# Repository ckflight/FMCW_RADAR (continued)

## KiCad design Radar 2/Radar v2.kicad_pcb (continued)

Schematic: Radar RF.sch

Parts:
C32, C35, C36, C41, C43, C44, C46, C49, C50, C51, C56, C58, C59, C66, C70, C80, C84, C85, C86, C87, C88, C109, C110: 100nF; SMD_0402
C33: 470pF; SMD_0402
C37, C38, C42: 18pF; SMD_0402
C39, C40, C52, C60, C61, C67, C68, C76: 10pF; SMD_0402
C45, C47, C48, C53, C79: 100pF; SMD_0402
C55: 330nF; SMD_0402
C57, C73, C74, C75, C77, C78: 10nF; SMD_0402
C62: 2.2nF; SMD_0402
C63, C64, C89: 10uF; SMD_0603
C65, C71: DNP; SMD_0402
C69: 2.2uF; SMD_0402
C72, C81, C82, C90: 1nF; SMD_0402
C83: 0.5pF; SMD_0402
D9, D10: Led_Diode; Diode_0603
L1, L4, L5, L8, L9: BLM18PG181SN1D; SMD_0603
L2, L3: 2.2uH; SMD_0603
L6: LQW18ANR10J00D; SMD_0603
L7: 0.6nH; SMD_0402
R2, R3, R33, R35: 0; SMD_0402
R25, R29, R59: 50; SMD_0402
R26: 5.49K; SMD_0402
R27, R28, R31, R75: DNP; SMD_0402
R30, R39, R40, R46, R49, R56, R79, R80: 1K; SMD_0402
R32: 240; SMD_0402
R36, R37: 4.7K; SMD_0402
R38: 100K; SMD_0402
R41, R42: 10K; SMD_0402
R43: 1.8; SMD_0402
R44, R45: 910; SMD_0402
R47, R48: 130; SMD_0402
R50, R51: 4.99K; SMD_0402
R52, R77, R78: 16.7; SMD_0402
R57: 0 to 27; SMD_0402
R58: 30K; SMD_0402
R76: 100; SMD_0402
U5, U10, U11, U14, U16, U24, U26, U34, U36, U46: Check_Point; SolderPad_1_1.5mm_SMD_Circle
U6: SG-210STF; Crystal_2.5x2mm
U7, U13: 5400BL15B050E; Balun_5400BL15B050E
U8: ADF4158; LFCSP24_4x4mm_P0.5mm_1EXP_2.5x2.5mm
U9: ADL5801; LFCSP24_4x4mm_P0.5mm_1EXP_2.5x2.5mm
U12: TLV172; SC70_5
U15: LT6232; SSOP16_3.9x4.9mm_P0.635mm
U17: HMC431LP4; QFN24_4x4mm_P0.5mm_1EXP_2.7x2.7mm
U18: TRF37A75; WSON8_2x2mm_P0.5mm_1EXP_0.9x1.6mm
U19, U27: PAT1220-C-6DB; PAT1220_6dB
U20: SKY65404; SKY65404_31
U21: TQP5523; QFN20_4x4mm_P0.5mm_1EXP_2.5x2.5mm
U22, U30: SMA_Connector
U23, U28, U42, U43, U44: MITERED_BEND; Mitered_Bend_0.33mm_90
U29: Directional_Coupler; Directional_Coupler_15dB

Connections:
+2.5: R46.2, R47.2, R48.1, R49.2, U15.3 (+), U15.5 (+); also elsewhere on the board
+3.0: L4.2; also elsewhere on the board
+3.3: C32.1, C35.1, C36.1, C37.1, C38.1, C109.1, L9.1, U6.1 (ST), U6.4 (VCC), U8.6 (AVDD), U8.7 (AVDD), U8.8 (AVDD), U8.18 (SDVDD), U8.19 (DVDD); also elsewhere on the board
+5: C41.2, C43.2, C44.2, C45.2, C47.2, C56.2, C58.1, C66.2, C71.1, C110.2, L1.2, L5.1, L8.1, R25.1, R29.2, R30.1, U9.7 (VPLO), U9.13 (VPDT), U9.18 (VPRF), U9.24 (VPLO), U15.4 (V+); also elsewhere on the board
+10: C59.1, U12.5 (V+); also elsewhere on the board
/Radar RF/LNA_3.3: C84.1, C86.1, D10.2 (A), L7.2, L9.2, R76.1
ADF_CE: U8.13 (CE); also elsewhere on the board
ADF_CLK: U8.14 (CLK); also elsewhere on the board
ADF_DATA: U8.15 (DATA); also elsewhere on the board
ADF_LE: U8.16 (LE); also elsewhere on the board
ADF_MUXOUT: U8.17 (MUX_OUT), U36.1; also elsewhere on the board
ADF_TXDATA: U8.12 (TXDATA); also elsewhere on the board
DAC_OUT1: R75.1, U11.1; also elsewhere on the board
DET_OUT: R58.1, U21.10 (DET), U24.1; also elsewhere on the board
GND: C32.2, C35.2, C36.2, C37.2, C38.2, C41.1, C42.2, C43.1, C44.1, C45.1, C46.2, C47.1, C48.2, C49.1, C50.1, C51.1, C53.1, C56.1, C57.2, C58.2, C59.2, C65.2, C66.1, C69.2, C70.2, C71.2, C75.2, C76.2, C79.2, C80.2, C83.2, C84.2, C85.2, C86.2, C87.1, C88.1, C89.1, C109.2, C110.1, R26.2, R31.2, R32.1, R37.2, R56.2, R58.2, R59.2, R79.2, R80.2, U6.2 (GND), U7.2 (GND), U7.5 (GND), U8.1 (CPGND), U8.2 (AGND), U8.3 (AGND), U8.10 (DGND), U8.11 (SDGND), U8.25 (EXP), U9.1 (GND), U9.2 (GND), U9.5 (GND), U9.6 (GND), U9.8 (GND), U9.12 (GND), U9.14 (GND), U9.17 (GND), U9.19 (GND), U9.23 (GND), U9.25 (EXP), U12.2 (V-), U13.2 (GND), U13.5 (GND), U15.13 (V-), U17.15 (GND), U17.25 (EXP), U18.3 (NC), U18.4 (NC), U18.5 (PWDN), U18.6 (NC), U18.8 (NC), U18.9 (GND), U19.3 (GND), U20.2 (GND), U20.5 (GND), U20.7 (EXP), U21.1 (GND), U21.2 (GND), U21.4 (GND), U21.11 (GND), U21.12 (GND), U21.14 (GND), U21.15 (GND), U21.16 (GND), U21.17 (GND), U21.21 (EXP), U22.2, U22.3, U22.4, U22.5, U27.3 (GND), U30.2, U30.3, U30.4, U30.5, U46.1; also elsewhere on the board
IF+: L2.1, R29.1, U5.1, U9.20 (IFOP)
IF-: L3.1, R25.2, U9.21 (IFON), U16.1
IFF+: R44.1, R50.1, U15.16; also elsewhere on the board
IFF-: R45.2, R51.1, U15.10; also elsewhere on the board
MIXER_EN: U9.9 (ENBL); also elsewhere on the board
MIXER_LO: U7.1 (IN), U23.2
unnamed: C33.1, U8.9 (REF_IN)
unnamed: C33.2, U6.3 (OUT)
unnamed: C39.1, U9.3 (LOIP)
unnamed: C39.2, U7.4 (OUTN)
unnamed: C40.1, U9.4 (LOIN)
unnamed: C40.2, U7.3 (OUTP)
unnamed: C42.1, C46.1, L1.1, U8.22 (VP)
unnamed: C48.1, U8.4 (RFINB)
unnamed: C49.2, C51.2, R27.2, R30.2, R31.1, U9.10 (VSET)
unnamed: C50.2, C53.2, R27.1, U9.11 (DETO)
unnamed: C52.1, U8.5 (RFINA)
unnamed: C52.2, U44.2
unnamed: C55.1, C57.1, R33.1, U8.24 (CP), U10.1
unnamed: C55.2, R28.2, R32.2
unnamed: C60.1, U13.4 (OUTN)
unnamed: C61.1, U13.3 (OUTP)
unnamed: C62.1, C63.2, L2.2
unnamed: C62.2, C64.2, L3.2
unnamed: C63.1, R39.1
unnamed: C64.1, R40.1
unnamed: C65.1, R38.1, U14.1, U17.22 (VTUNE)
unnamed: C67.1, R2.1, R41.2, U15.1, U26.1
unnamed: C67.2, R39.2, R41.1, U15.2 (-)
unnamed: C68.1, R3.1, R42.2, U15.7, U34.1
unnamed: C68.2, R40.2, R42.1, U15.6 (-)
unnamed: C69.1, C70.1, L4.1, U17.20 (VCC)
unnamed: C72.1, L6.1, U18.7 (RFOUT)
unnamed: C72.2, U42.2
unnamed: C73.1, C77.2, R44.2
unnamed: C73.2, R2.2
unnamed: C74.1, C78.2, R45.1
unnamed: C74.2, R3.2
unnamed: C75.1, C76.1, L6.2, R43.2
unnamed: C77.1, R47.1, U15.14 (+)
unnamed: C78.1, R48.2, U15.12 (+)
unnamed: C79.1, C80.1, L5.2, R43.1, U18.1 (VCC)
unnamed: C81.1, U20.4 (RF_OUT)
unnamed: C81.2, U18.2 (RFIN)
unnamed: C82.1, U21.3 (RFIN)
unnamed: C82.2, U19.2 (OUT)
unnamed: C83.1, U20.3 (RF_IN), U22.1
unnamed: C85.1, R57.2, U21.20 (VCC1)
unnamed: C87.2, C88.2, C89.2, L8.2, R57.1, U21.18 (VCC3), U21.19 (VCC2)
unnamed: C90.1, U29.1 (IN)
unnamed: C90.2, U21.13 (RFOUT)
unnamed: D9.1 (K), R79.1
unnamed: D10.1 (K), R80.1
unnamed: L7.1, U20.6 (VCC)
unnamed: R26.1, U8.23 (RSET)
unnamed: R28.1, U8.20 (SW1)
unnamed: R33.2, R75.2, U12.1 (+)
unnamed: R35.1, R38.2, U12.4
unnamed: R35.2, R36.1
unnamed: R36.2, R37.1, U12.3 (-)
unnamed: R46.1, R50.2, U15.15 (-)
unnamed: R49.1, R51.2, U15.11 (-)
unnamed: R52.1, U17.16 (RFOUT)
unnamed: R52.2, R77.1, R78.2
unnamed: R59.1, U29.4 (TRM)
unnamed: R76.2, U20.1 (V_ENA)
unnamed: R77.2, U19.1 (IN)
unnamed: R78.1, U43.2
unnamed: U13.1 (IN), U42.1
unnamed: U23.1, U28.1
unnamed: U27.1 (IN), U29.3 (CPL)
unnamed: U27.2 (OUT), U28.2
unnamed: U29.2 (OUT), U30.1
unnamed: U43.1, U44.1
PA_EN: D9.2 (A), R56.1, U21.5 (PA_EN); also elsewhere on the board
RFIN: C60.2, U9.15 (RFIN)
RFIP: C61.2, U9.16 (RFIP)

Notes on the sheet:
Scale 3.3V DAC output to 10V
Scale 5V PLL output to 10V
If DAC will be used change R35(0) with 4.7K to make gain 3
RC filter makes it noisy. I just placed 100K series resistor to filter noise.
Max 0dBm -4dBm input
-4dBm
29 to 37dB, typ. 32dB Gain OP1dB 31dBm Pout = 22 to 27dBm Pout = 21dBm 5V, 300mA
WYE -6dBm resistive splitter Zo/3 each apprx. 17 ohm
-10dBm
100mW rating
TX ANTENNA
16dB Directional Coupler
-16dB
Pout = 6 to 11 dBm - 6 dB = 0 to 5 dBm
Pout = 22 to 27dBm - 16dB = 6 to 11 dBm
RX ANTENNA
Max Input Power: 1dBm NF: 1dB Gain: 12dB at 6GHz IIP3: 9 dBm IP1dB: -4 dBm
Max 1dBm input to LNA
Max Input Power: 10 dBm NF: 4.0 dB Gain: 11 dB at 6 GHz OIP3: 23 dBm OP1dB: 12 dBm
-1dB Insertion Loss
Idd = 32mA max
Pout 2dBm @3v, 27mA
PI Type Attenuator Network 1 and 2 can be both in/out, directionless
@3.0 max 15mA
@5.0v, max 100mA
IIP3 28.5 dBm IP1dB 11dBm for 5-6GHz LO drive 0dBm @5v, max 200mA typ 130mA
Input 2 MHz LC low pass filter. 10uF for AC coupling capactior to remove DC offset. 1st stage opamp is amplifier. 2nd stage opamp is sallen key high pass filter IMPORTANT NOTE: Sallen Key filter calculator has oscillation calculation to show if it oscillates. Be careful when changing the numbers Th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
ADF4158 is Freq. Synthesizer to form a PLL topology. It requires a referance clock and an external VCO. It is not a PLL itself. It is used to drive VCO in a way the user wants. So it takes ref clock and VCO output and generates voltage through charge pump to generate the waveform wanted.(sawtooth e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
50 Ohm to 50 Ohm Balun for Single to Differential
4.5 to 5.25 range
30MHz
2.8 to 5.0 range
+2dBm Output
330nF 10nF 240 Ohm has no oscillation
Sallen Key filter requires isolation resistor to prevent oscillation. The capacitive load makes it unstable. To attenuate the peak value of 1.4MHz oscillation i changed differential to single ended 1K to 100 Ohm and added gain.

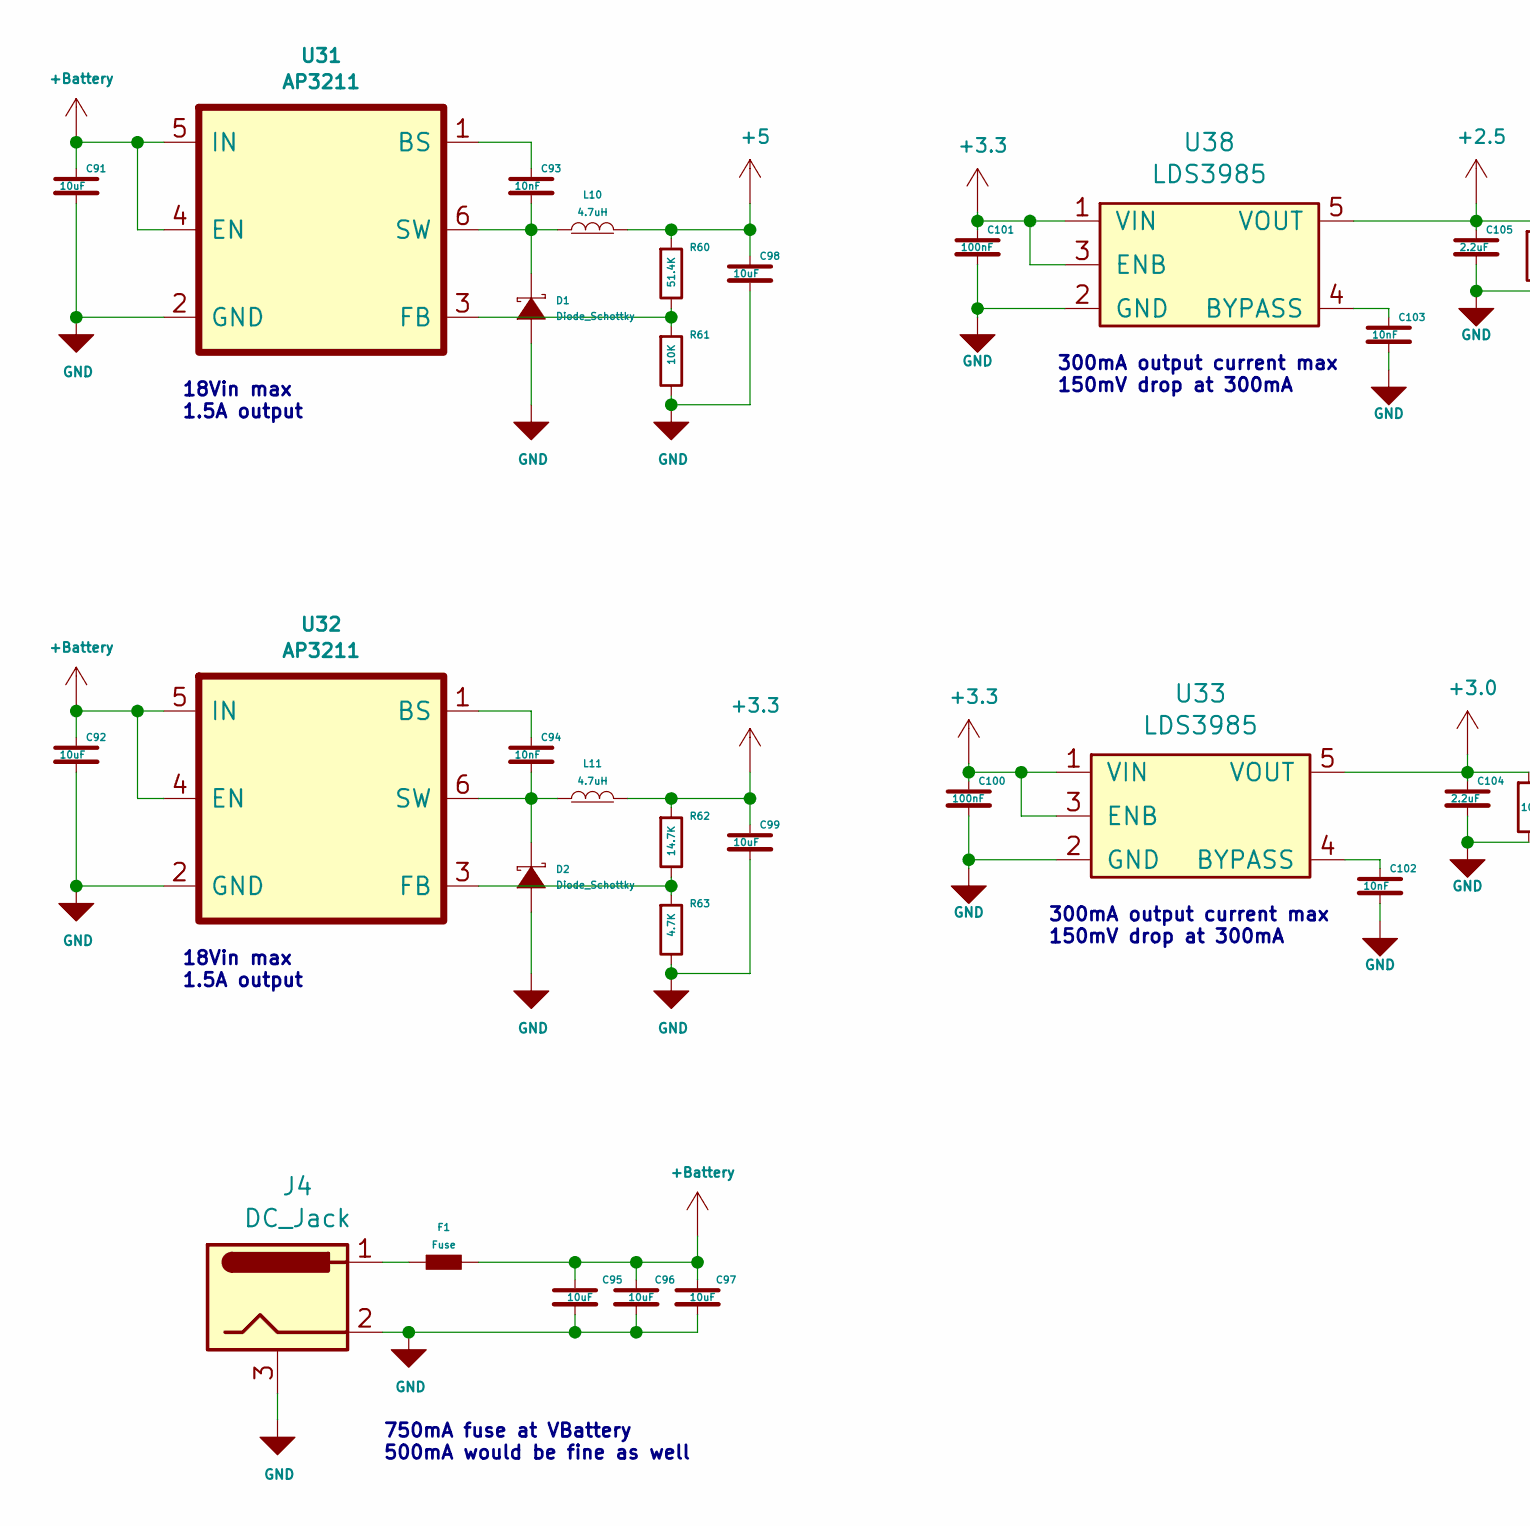
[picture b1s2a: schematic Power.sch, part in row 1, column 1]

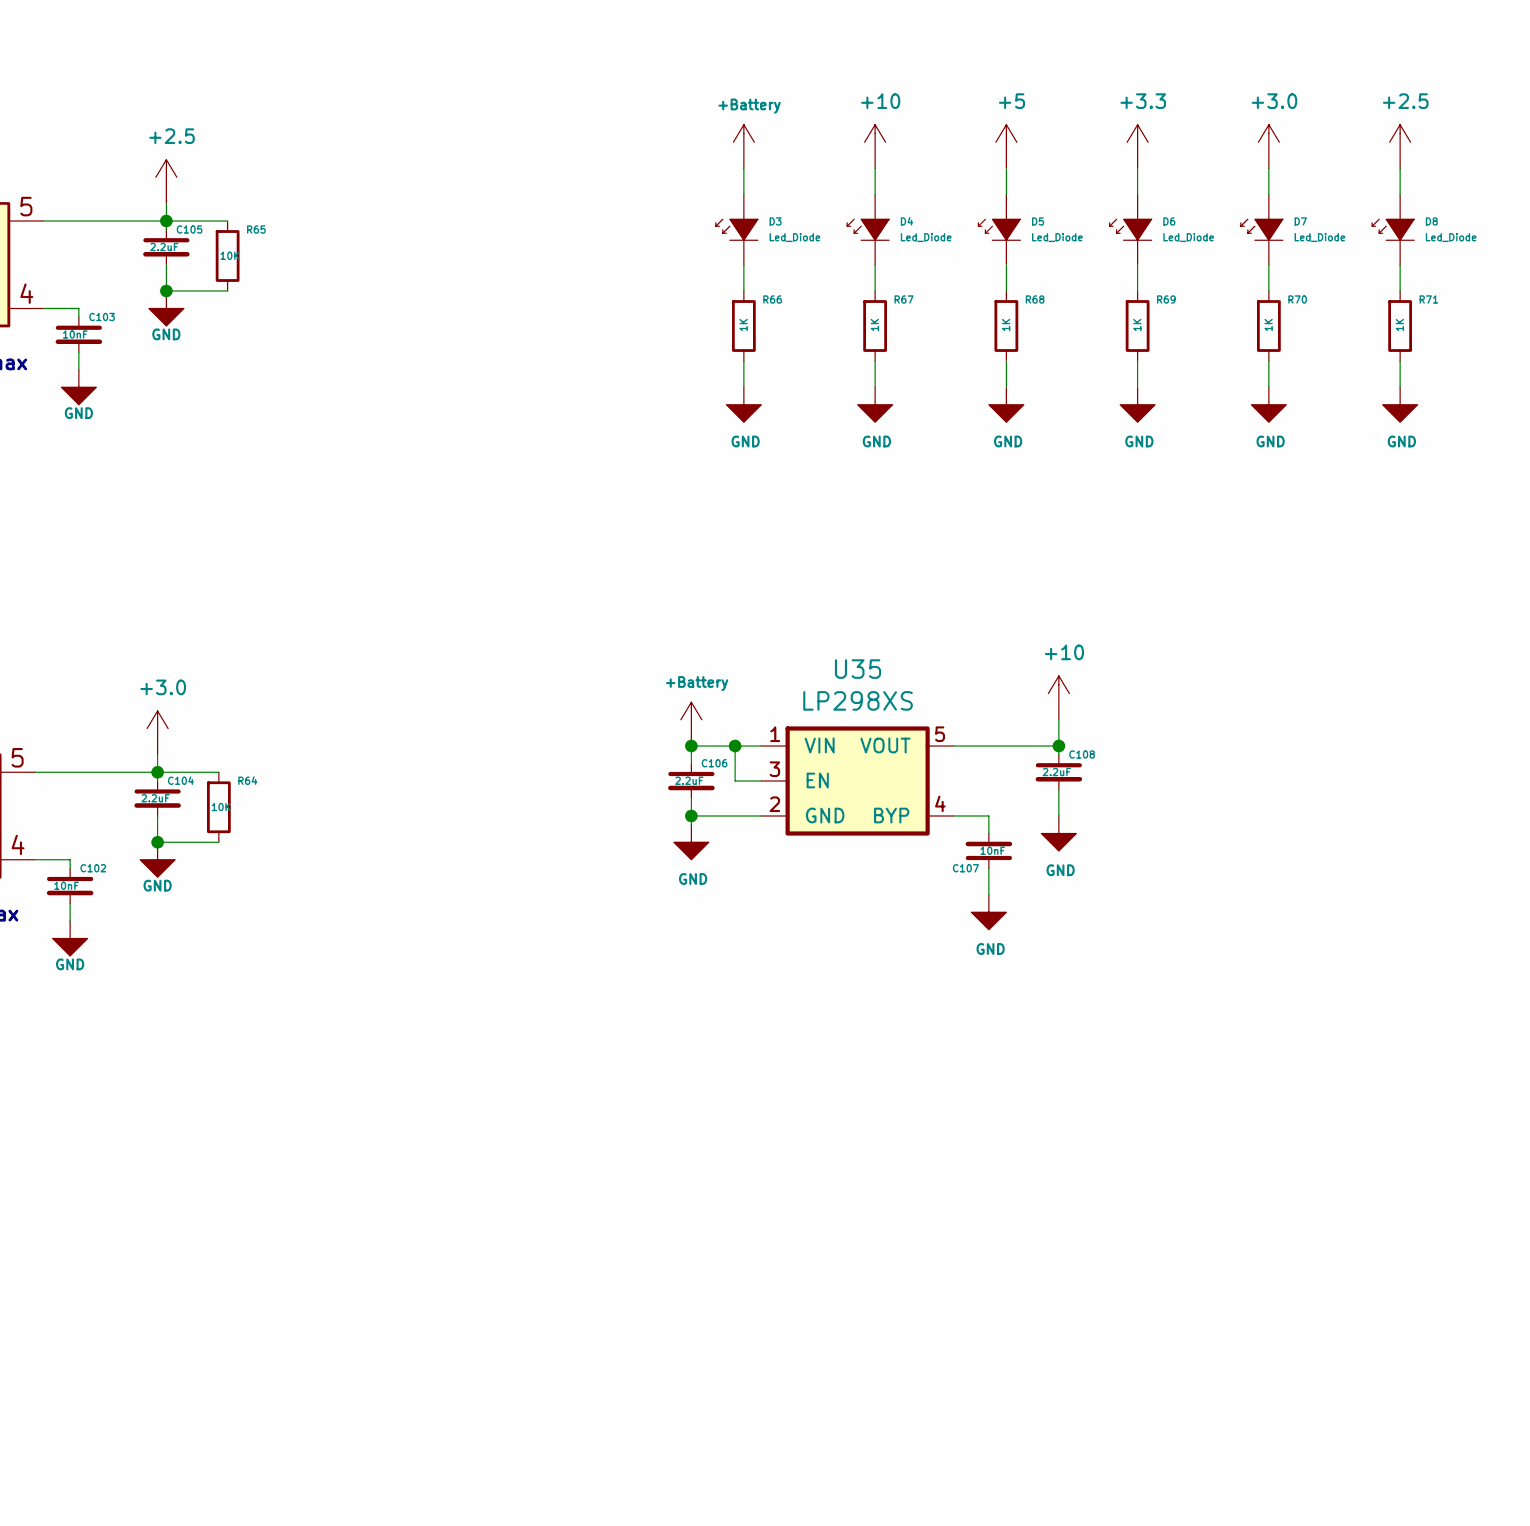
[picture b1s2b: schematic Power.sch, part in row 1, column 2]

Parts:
C91, C92, C95, C96, C97, C98, C99: 10uF; SMD_0603
C93, C94, C102, C103, C107: 10nF; SMD_0402
C100, C101: 100nF; SMD_0402
C104, C105, C106, C108: 2.2uF; SMD_0603
D1, D2: Diode_Schottky; Diode_SDM2U30CSP_7
D3, D4, D5, D6, D7, D8: Led_Diode; Diode_0603
F1: Fuse; SMD_0805
J4: DC_Jack; BarrelJack
L10, L11: 4.7uH; SMD_0805
R60: 51.4K; SMD_0402
R61, R64, R65: 10K; SMD_0402
R62: 14.7K; SMD_0402
R63: 4.7K; SMD_0402
R66, R67, R68, R69, R70, R71: 1K; SMD_0402
U31, U32: AP3211; SOT23_6
U33, U38: LDS3985; SOT23_5
U35: LP298XS; SOT23_5

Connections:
+2.5: C105.1, D8.2 (A), R65.1, U38.5 (VOUT); also elsewhere on the board
+3.0: C104.1, D7.2 (A), R64.1, U33.5 (VOUT); also elsewhere on the board
+3.3: C99.1, C100.1, C101.1, D6.2 (A), L11.2, R62.1, U33.1 (VIN), U33.3 (ENB), U38.1 (VIN), U38.3 (ENB); also elsewhere on the board
+5: C98.1, D5.2 (A), L10.2, R60.1; also elsewhere on the board
+10: C108.1, D4.2 (A), U35.5 (VOUT); also elsewhere on the board
+Battery: C91.1, C92.1, C95.1, C96.1, C97.1, C106.1, D3.2 (A), F1.2, U31.4 (EN), U31.5 (IN), U32.4 (EN), U32.5 (IN), U35.1 (VIN), U35.3 (EN)
GND: C91.2, C92.2, C95.2, C96.2, C97.2, C98.2, C99.2, C100.2, C101.2, C102.2, C103.2, C104.2, C105.2, C106.2, C107.1, C108.2, D1.2 (A), D2.2 (A), J4.2, J4.3, R61.2, R63.2, R64.2, R65.2, R66.2, R67.2, R68.2, R69.2, R70.2, R71.2, U31.2 (GND), U32.2 (GND), U33.2 (GND), U35.2 (GND), U38.2 (GND); also elsewhere on the board
unnamed: C93.1, U31.1 (BS)
unnamed: C93.2, D1.1 (C), L10.1, U31.6 (SW)
unnamed: C94.1, U32.1 (BS)
unnamed: C94.2, D2.1 (C), L11.1, U32.6 (SW)
unnamed: C102.1, U33.4 (BYPASS)
unnamed: C103.1, U38.4 (BYPASS)
unnamed: C107.2, U35.4 (BYP)
unnamed: D3.1 (K), R66.1
unnamed: D4.1 (K), R67.1
unnamed: D5.1 (K), R68.1
unnamed: D6.1 (K), R69.1
unnamed: D7.1 (K), R70.1
unnamed: D8.1 (K), R71.1
unnamed: F1.1, J4.1
unnamed: R60.2, R61.1, U31.3 (FB)
unnamed: R62.2, R63.1, U32.3 (FB)

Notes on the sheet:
300mA output current max 150mV drop at 300mA
18Vin max 1.5A output
750mA fuse at VBattery 500mA would be fine as well

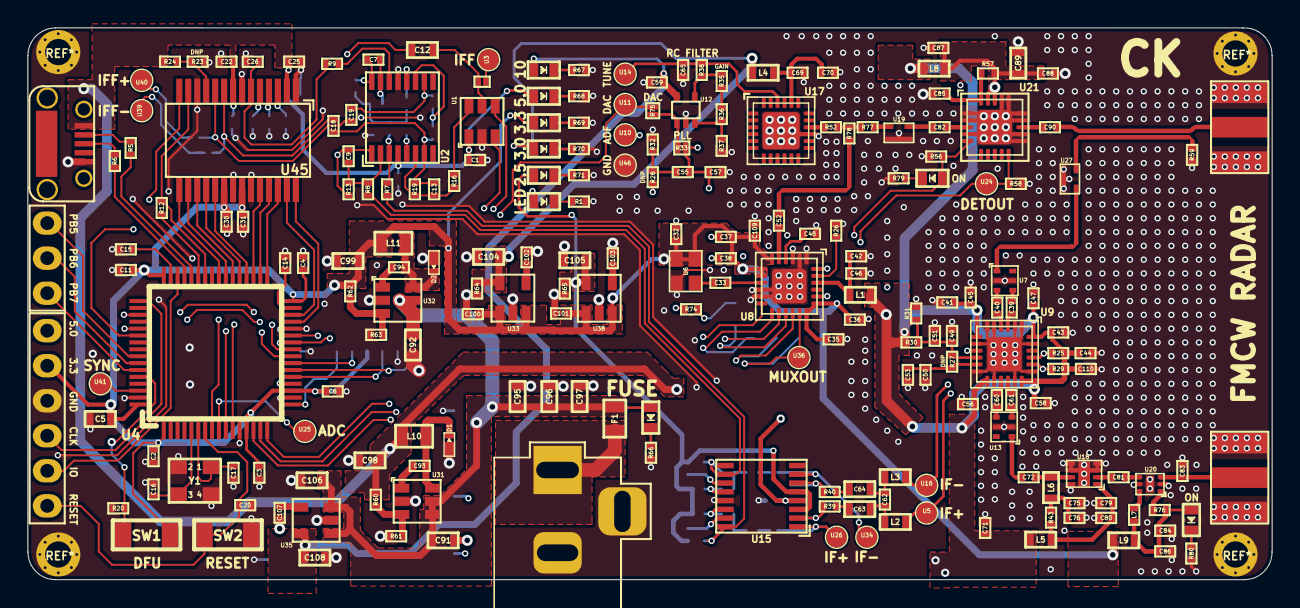
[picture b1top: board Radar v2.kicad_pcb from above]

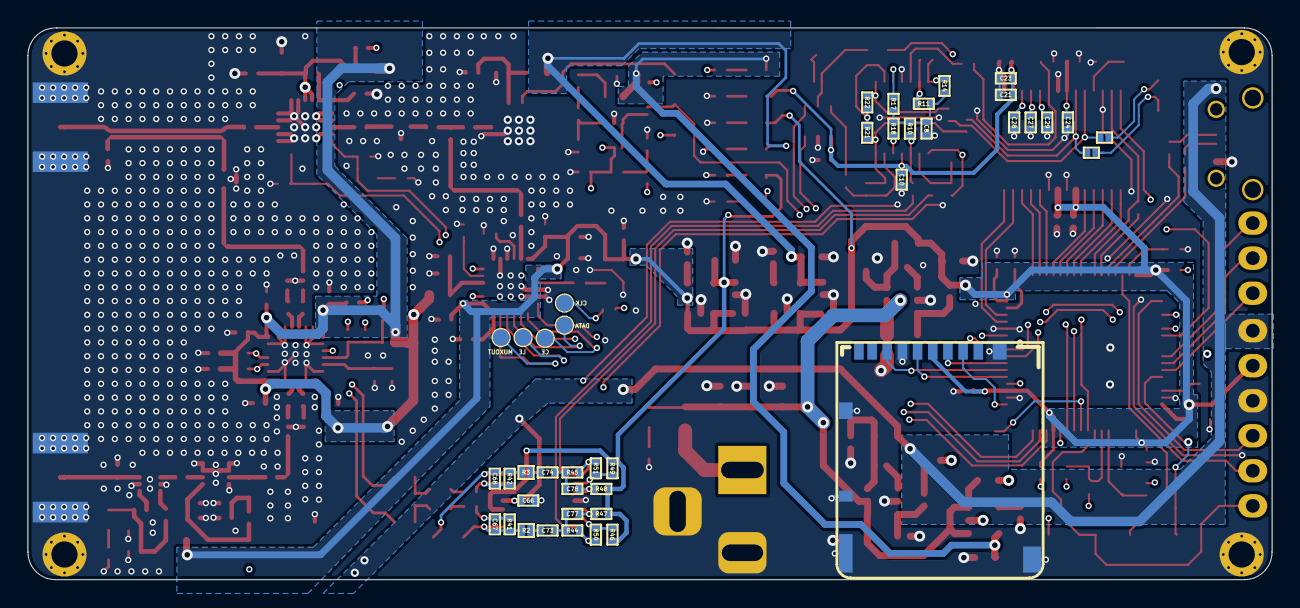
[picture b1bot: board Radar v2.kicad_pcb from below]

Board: 4 copper layers, 90.2 x 40.0 mm, 264 parts (42 on the bottom side), 173 nets.

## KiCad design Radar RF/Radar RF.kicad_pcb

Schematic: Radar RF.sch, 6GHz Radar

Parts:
C12, C13, C14, C21, C22, C28, C37, C38, C39, C40, C43, C45, C46, C48, C50, C51, C52, C53, C64, C67, C69, C74, C75: 100nF; SMD_0402
C15, C16, C18, C59, C68: 18pF; SMD_0402
C17: 2.2nF; SMD_0402
C19, C20, C26: 330nF; SMD_0402
C23, C41, C42, C47, C65: 100pF; SMD_0402
C24, C25, C35, C36, C54, C55, C62: 10pF; SMD_0402
C27: 2pF; SMD_0402
C29, C31, C32, C33, C34, C44: 470pF; SMD_0402
C30, C56, C61: 10nF; SMD_0402
C49, C57, C63, C71: 2.2uF; SMD_0402
C58, C66: DNP; SMD_0402
C60, C72: 1000pF; SMD_0402
C70: 10uF; SMD_0603
C73: 0.5pF; SMD_0402
D1, D2, D3: Led_Diode; Diode_0603
J1: Connector_02x15; PinHeader_2x15_DF12B(5.0)-30DP-0.5V(86)
L1, L2: 2.2uH; SMD_0603
L3: BLM18PG181SN1D; SMD_0603
L4: LQW15AN9N9J80D; SMD_0402
L5: 0.6nH; SMD_0402
R1, R16, R19, R29, R39, R40, R42: 1K; SMD_0402
R2, R3, R15, R27, R30: DNP; SMD_0402
R4, R12, R22, R35, R43: 0; SMD_0402
R5, R6: 549; SMD_0402
R7: 5.49K; SMD_0402
R8: 69.8; SMD_0402
R9, R10, R34: 10K; SMD_0402
R11: 240; SMD_0402
R13, R14: 910; SMD_0402
R17, R18: 130; SMD_0402
R20, R21: 4.99K; SMD_0402
R23, R24, R26: 4.7K; SMD_0402
R25, R28, R41: 50; SMD_0402
R31, R32, R33: 18; SMD_0402
R36: 0 to 27; SMD_0402
R37: 30K; SMD_0402
R38: 100; SMD_0402
U1: LT6232; SSOP16_3.9x4.9mm_P0.635mm
U2: ADF4158; LFCSP24_4x4mm_P0.5mm_1EXP_2.5x2.5mm
U3: SG-210STF; Crystal_2.5x2mm
U4, U9, U23: MITERED_BEND; Mitered_Bend_0.34mm_90
U5: MITERED_BEND; Mitered_Bend_0.34mm_45
U6, U13: 5400BL15B050E; Balun_5400BL15B050E
U7: TLV172; SC70_5
U8: MITERED_BEND; Mitered_Bend_0.34mm_45_Mirrored
U10: ADL5801; LFCSP24_4x4mm_P0.5mm_1EXP_2.5x2.5mm
U11: HMC431LP4; QFN24_4x4mm_P0.5mm_1EXP_2.7x2.7mm
U12: LDS3985; SOT23_5
U14, U19: PAT1220-C-6DB; PAT1220_6dB
U15: TRF37A73; WSON8_2x2mm_P0.5mm_1EXP_0.9x1.6mm
U16: TQP5523; QFN20_4x4mm_P0.5mm_1EXP_2.5x2.5mm
U17: MCP1700; SOT23_3
U18: SKY65404; SKY65404_31
U20: Directional_Coupler; Directional_Coupler_15dB
U21, U22: SMA_Connector
U24: IF+_PAD; SolderPad_1_1.5mm_SMD_Rectangle
U25: IF-_PAD; SolderPad_1_1.5mm_SMD_Rectangle
U26, U27: GND; SolderPad_1_1.5mm_SMD_Rectangle

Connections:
25MHz: C29.1, U2.9 (REF_IN)
+2V5: C57.1, R16.2, R17.2, R18.1, R19.2, R34.1, U1.3 (+), U1.5 (+), U12.5 (VOUT)
+3V0: C49.1, C51.1, C58.1, C71.1, C74.1, C75.1, D3.2 (A), L3.1, L5.2, R38.1, U11.20 (VCC), U17.2 (VOUT); also elsewhere on the board
+3V3: C12.1, C13.1, C14.1, C15.1, C16.1, C22.1, C53.1, C63.1, D2.2 (A), J1.4, J1.5, U2.6 (AVDD), U2.7 (AVDD), U2.8 (AVDD), U2.18 (SDVDD), U2.19 (DVDD), U3.1 (ST), U3.4 (VCC), U12.1 (VIN), U12.3 (ENB), U17.3 (VIN); also elsewhere on the board
+5V: C18.1, C21.1, C28.2, C38.2, C39.2, C40.2, C41.2, C42.2, C48.2, C50.2, C52.1, C67.2, C69.2, C70.2, D1.2 (A), J1.26, J1.27, J1.28, J1.29, R25.1, R28.2, R29.1, R36.1, U1.4 (V+), U2.22 (VP), U10.7 (VPLO), U10.13 (VPDT), U10.18 (VPRF), U10.24 (VPLO), U16.18 (VCC3), U16.19 (VCC2); also elsewhere on the board
+10V: C37.1, J1.22, U7.5 (V+)
ADF_CE: J1.10, U2.13 (CE)
ADF_CLK: J1.11, U2.14 (CLK)
ADF_DATA: J1.12, U2.15 (DATA)
ADF_LE: J1.13, U2.16 (LE)
ADF_MUXOUT: J1.14, U2.17 (MUX_OUT)
ADF_TXDATA: J1.9, U2.12 (TXDATA)
DAC_OUT1: J1.2, R15.1
DET_OUT: J1.8, R37.1, U16.10 (DET)
GND: C12.2, C13.2, C14.2, C15.2, C16.2, C18.2, C21.2, C22.2, C23.2, C28.1, C30.2, C37.2, C38.1, C39.1, C40.1, C41.1, C42.1, C43.1, C44.2, C45.1, C46.1, C47.1, C48.1, C49.2, C50.1, C51.2, C52.2, C53.2, C56.2, C57.2, C58.2, C61.2, C62.2, C63.2, C64.2, C65.2, C66.2, C67.1, C69.1, C70.1, C71.2, C73.2, C74.2, C75.2, J1.1, J1.3, J1.6, J1.16, J1.17, J1.20, J1.21, J1.23, J1.24, J1.25, J1.30, R1.2, R7.2, R11.1, R24.2, R30.2, R34.2, R37.2, R39.2, R40.2, R41.2, R42.2, U1.13 (V-), U2.1 (CPGND), U2.2 (AGND), U2.3 (AGND), U2.10 (DGND), U2.11 (SDGND), U2.25 (EXP), U3.2 (GND), U6.2 (GND), U6.5 (GND), U7.2 (V-), U10.1 (GND), U10.2 (GND), U10.5 (GND), U10.6 (GND), U10.8 (GND), U10.12 (GND), U10.14 (GND), U10.17 (GND), U10.19 (GND), U10.23 (GND), U10.25 (EXP), U11.15 (GND), U11.25 (EXP), U12.2 (GND), U13.2 (GND), U13.5 (GND), U14.3 (GND), U15.3 (NC), U15.4 (NC), U15.5 (PWDN), U15.6 (NC), U15.8 (NC), U15.9 (GND), U16.1 (GND), U16.2 (GND), U16.4 (GND), U16.11 (GND), U16.12 (GND), U16.14 (GND), U16.15 (GND), U16.16 (GND), U16.17 (GND), U16.21 (EXP), U17.1 (GND), U18.2 (GND), U18.5 (GND), U18.7 (EXP), U19.3 (GND), U21.2, U21.3, U21.4, U21.5, U22.2, U22.3, U22.4, U22.5, U26.1, U27.1; also elsewhere on the board
IF+: R2.1, R4.1, R28.1, U10.20 (IFOP)
IF-: R3.2, R25.2, R43.2, U10.21 (IFON)
IFN_Filtered: J1.19, R14.2, R21.1, U1.10
IFP_Filtered: J1.18, R13.1, R20.1, U1.16
MIXER_ENB: J1.15, U10.9 (ENBL)
MIXER_LO: U4.2, U6.1 (IN)
unnamed: C17.1, C19.2, L1.2
unnamed: C17.2, C20.2, L2.2
unnamed: C19.1, R5.1
unnamed: C20.1, R6.1
unnamed: C23.1, U2.4 (RFINB)
unnamed: C24.1, C31.2, R9.2, U1.1
unnamed: C24.2, R5.2, R9.1, U1.2 (-)
unnamed: C25.1, C32.2, R10.2, U1.7
unnamed: C25.2, R6.2, R10.1, U1.6 (-)
unnamed: C26.1, C30.1, R12.1, U2.24 (CP)
unnamed: C26.2, R8.2, R11.2
unnamed: C27.1, U2.5 (RFINA)
unnamed: C27.2, R33.2
unnamed: C29.2, U3.3 (OUT)
unnamed: C31.1, C33.2, R13.2
unnamed: C32.1, C34.2, R14.1
unnamed: C33.1, R17.1, U1.14 (+)
unnamed: C34.1, R18.2, U1.12 (+)
unnamed: C35.1, U10.3 (LOIP)
unnamed: C35.2, U6.4 (OUTN)
unnamed: C36.1, U10.4 (LOIN)
unnamed: C36.2, U6.3 (OUTP)
unnamed 43: C43.2, C46.2, R27.2, R29.2, R30.1, U10.10 (VSET); also elsewhere on the board
unnamed: C44.1, R26.1, U11.22 (VTUNE)
unnamed 45: C45.2, C47.2, R27.1, U10.11 (DETO); also elsewhere on the board
unnamed: C54.1, U13.4 (OUTN)
unnamed: C55.1, U13.3 (OUTP)
unnamed: C56.1, U12.4 (BYPASS)
unnamed: C59.1, L4.1, U15.7 (RFOUT)
unnamed: C59.2, U23.1
unnamed: C60.1, U16.3 (RFIN)
unnamed: C60.2, U14.2 (OUT)
unnamed: C61.1, C62.1, C65.1, C66.1, L3.2, L4.2, U15.1 (VCC)
unnamed: C64.1, R36.2, U16.20 (VCC1)
unnamed: C68.1, U18.4 (RF_OUT)
unnamed: C68.2, U15.2 (RFIN)
unnamed: C72.1, U20.1 (IN)
unnamed: C72.2, U16.13 (RFOUT)
unnamed: C73.1, U18.3 (RF_IN), U22.1
unnamed 60: D1.1 (K), R39.1; also elsewhere on the board
unnamed 61: D2.1 (K), R40.1; also elsewhere on the board
unnamed 62: D3.1 (K), R42.1; also elsewhere on the board
unnamed: L1.1, R4.2
unnamed: L2.1, R43.1
unnamed: L5.1, U18.6 (VCC)
unnamed: R1.1, R35.2, U16.5 (PA_EN)
unnamed 67: R2.2, U24.1; also elsewhere on the board
unnamed 68: R3.1, U25.1; also elsewhere on the board
unnamed: R7.1, U2.23 (RSET)
unnamed: R8.1, U2.20 (SW1)
unnamed: R12.2, R15.2, U7.1 (+)
unnamed: R16.1, R20.2, U1.15 (-)
unnamed: R19.1, R21.2, U1.11 (-)
unnamed: R22.1, R26.2, U7.4
unnamed: R22.2, R23.1
unnamed: R23.2, R24.1, U7.3 (-)
unnamed: R31.1, U11.16 (RFOUT)
unnamed: R31.2, R32.2, R33.1
unnamed: R32.1, U14.1 (IN)
unnamed: R38.2, U18.1 (V_ENA)
unnamed: R41.1, U20.4 (TRM)
unnamed: U4.1, U8.1
unnamed: U5.1, U9.1
unnamed: U5.2, U8.2
unnamed: U13.1 (IN), U23.2
unnamed: U19.1 (IN), U20.3 (CPL)
unnamed: U9.2, U19.2 (OUT)
unnamed: U20.2 (OUT), U21.1
PA_EN: J1.7, R35.1
RFIN: C54.2, U10.15 (RFIN)
RFIP: C55.2, U10.16 (RFIP)

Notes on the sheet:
Scale 3.3V DAC output to 10V
Scale 5V PLL output to 10V
If DAC will be used change R22(0) with 4.7K to make gain 3
72KHz cutoff RC lowpass as PLL Loop Filter
+2dBm Output
Max 0dBm -4dBm input
-4dBm
32dB Gain Pout = 21 to 24dBm Pout = 21dBm 5V, 300mA
Delta -6dBm resistive splitter Zo/3 each apprx. 18 ohm
-10dBm
100mW rating
TX ANTENNA
16dB Directional Coupler
-16dB
Pout = 5 to 8 dBm - 6 dB = 0 to 2 dBm
Pout = 21 to 24dBm - 16dB = 5 to 8 dBm
RX ANTENNA
LNA NF: 1dB Gain: 13dB IIP3: 7dBm
Max 1dBm input to LNA
Max Input Power: 10 dBm NF: 4.5 dB Gain: 11 dB @ 5GHz
-1dB Insertion Loss
Idd = 32mA max
@3v, 27mA
@5v, 300mA
PI Type Attenuator Network 1 and 2 can be both in/out, directionless
@3v, max 15mA
@3v, max 65mA
@5v, max 200mA typ 130mA
Input has LC low pass filter. 330nF for AC coupling capactior to remove DC offset. 1st stage opamp is amplifier. 2nd stage opamp is sallen key high pass filter This filter both filteres high freq. and makes range compansation for objects at different distances.
250mA max 0.2v drop
300mA max
ADF4158 is Freq. Synthesizer to form a PLL topology. It requires a referance clock and an external VCO. It is not a PLL itself. It is used to drive VCO in a way the user wants. So it takes ref clock and VCO output and generates voltage through charge pump to generate the waveform wanted.(sawtooth e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
50 Ohm to 50 Ohm Balun for Single to Differential
I provide GND pad to send two cables parallel it can be used as return current if needed as a precausiton
If test the if without filtering i provided 0 ohm DNP pads to make necessary connections.

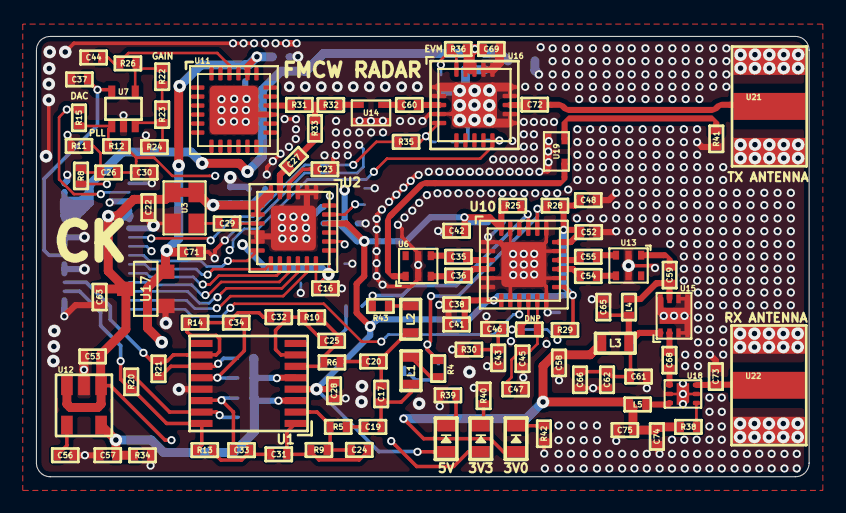
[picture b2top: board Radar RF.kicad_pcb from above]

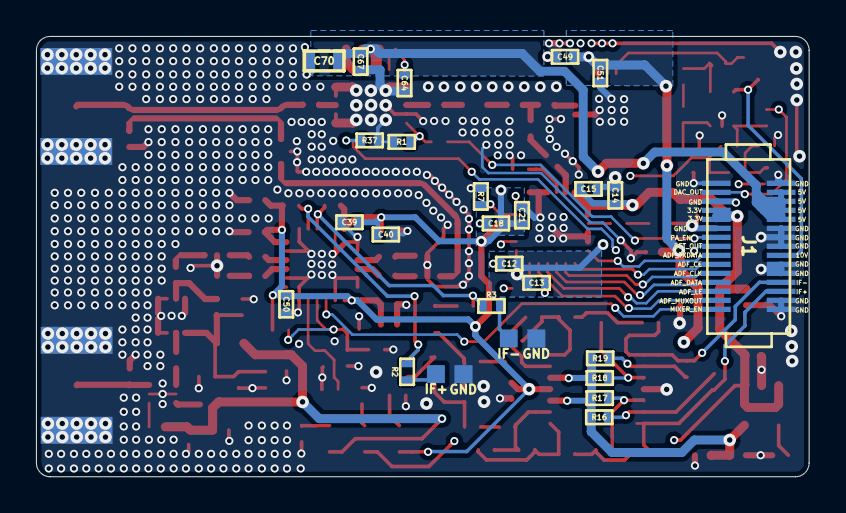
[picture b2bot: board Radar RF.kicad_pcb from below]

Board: 4 copper layers, 42.9 x 24.5 mm, 143 parts (28 on the bottom side), 92 nets.

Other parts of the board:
3V0, 3V3, 5V: Led_Diode; Diode_0603
DNP: DNP; SMD_0402
GND: GND; SolderPad_1_1.5mm_SMD_Rectangle
GND#2: GND; SolderPad_1_1.5mm_SMD_Rectangle
IF+: IF+_PAD; SolderPad_1_1.5mm_SMD_Rectangle
IF-: IF-_PAD; SolderPad_1_1.5mm_SMD_Rectangle

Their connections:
+3V0: 3V0.2; also elsewhere on the board
+3V3: 3V3.2; also elsewhere on the board
+5V: 5V.2; also elsewhere on the board
GND: GND.1, GND#2.1; also elsewhere on the board
unnamed 43: DNP.2; also elsewhere on the board
unnamed 45: DNP.1; also elsewhere on the board
unnamed 60: 5V.1; also elsewhere on the board
unnamed 61: 3V3.1; also elsewhere on the board
unnamed 62: 3V0.1; also elsewhere on the board
unnamed 67: IF+.1; also elsewhere on the board
unnamed 68: IF-.1; also elsewhere on the board
